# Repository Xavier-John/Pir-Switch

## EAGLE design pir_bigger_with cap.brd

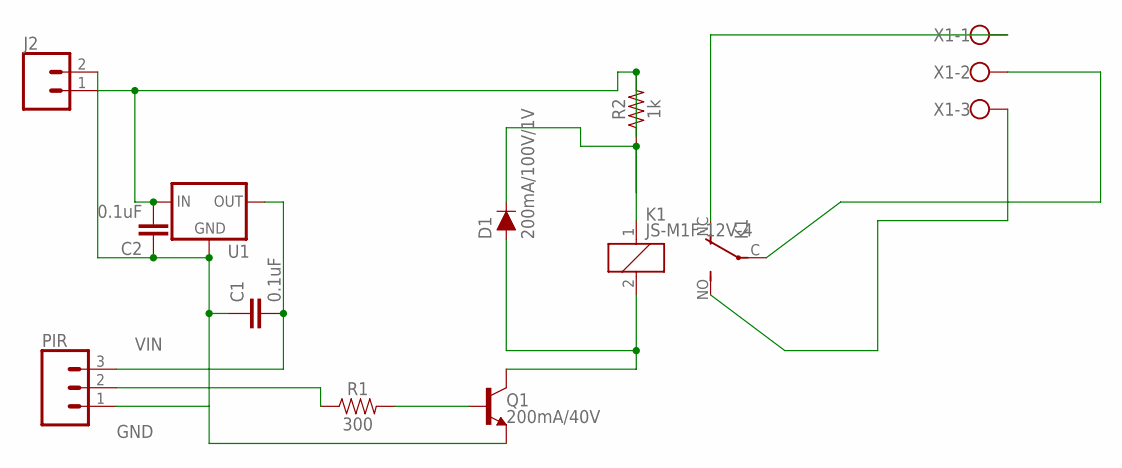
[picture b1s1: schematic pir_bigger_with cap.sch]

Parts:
C1, C2: 0.1uF; CAP-PTH-SMALL-KIT
D1: 200mA/100V/1V; DIODE-1N4148
J2: CONN_025MM; SCREWTERMINAL-5MM-2
K1: JS-M1F-12V-4; JS-M
PIR: CONN_03LONGPADS; 1X03_LONGPADS
Q1: 200mA/40V; TO-92
R1: 300; AXIAL-0.3
R2: 1k; AXIAL-0.3
U1: V_REG_78XXSINK; TO220-IGO
X1: W237-103

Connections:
GND: C1.1, C2.1, J2.2, PIR.1, Q1.1 (E), U1.GND
unnamed: C2.2, J2.1, R2.P$2 (2), U1.IN
unnamed: K1.C, X1.2
unnamed: PIR.2, R1.P$1 (1)
unnamed: Q1.2 (B), R1.P$2 (2)
unnamed: D1.A, K1.2, Q1.3 (C)
unnamed: K1.NC (O), X1.1
unnamed: K1.NO (S), X1.3
unnamed: D1.C, K1.1, R2.P$1 (1)
VIN: C1.2, PIR.3, U1.OUT

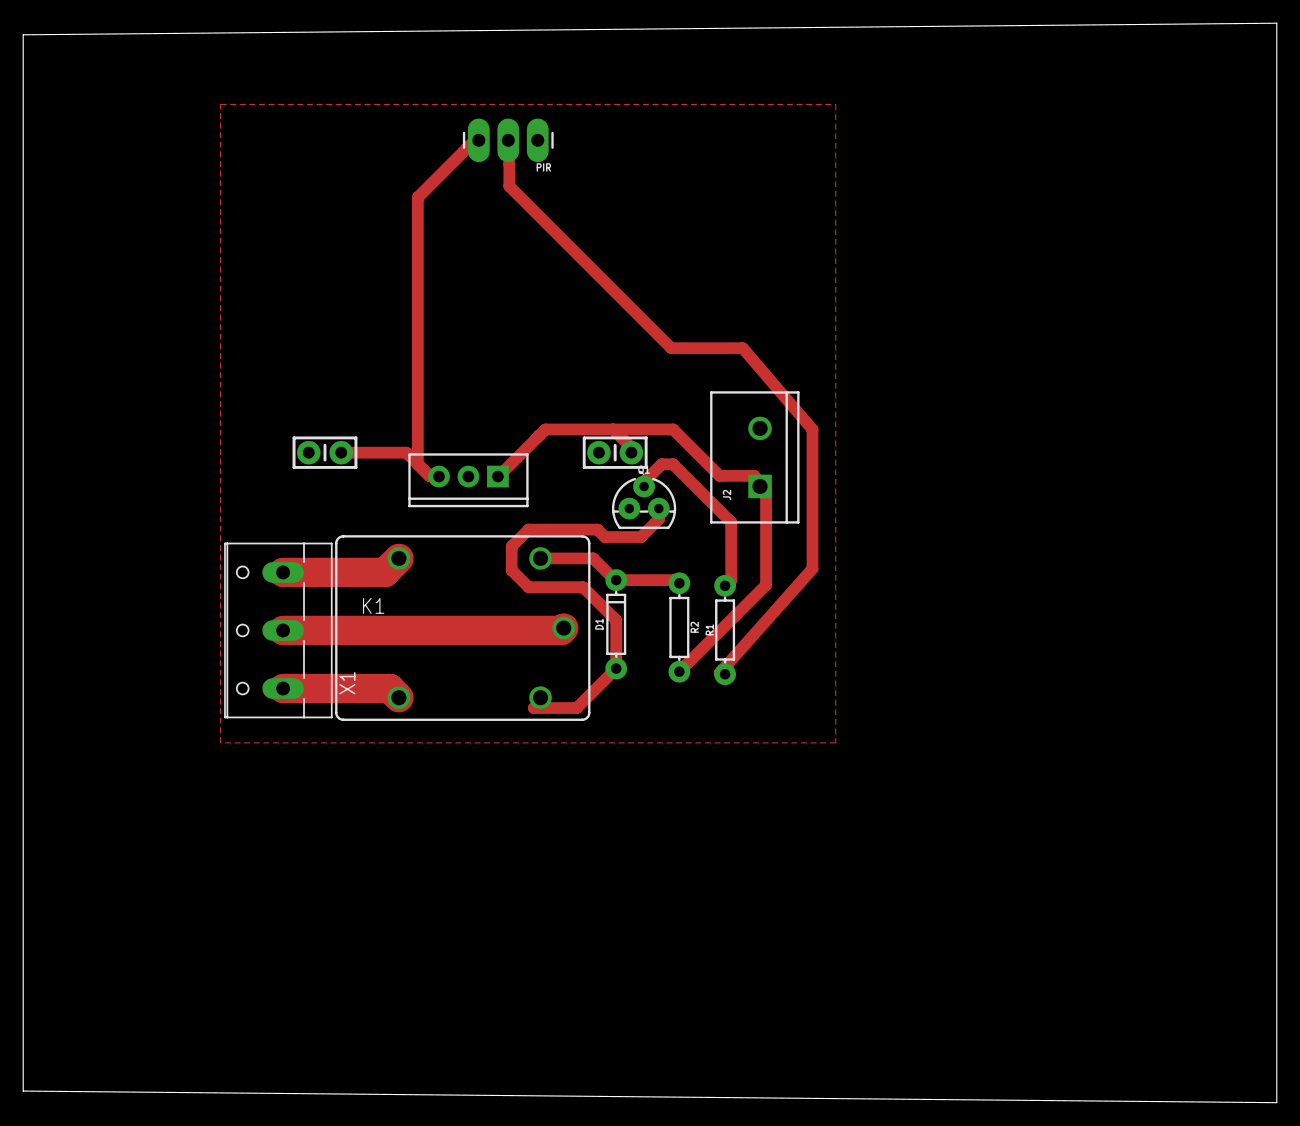
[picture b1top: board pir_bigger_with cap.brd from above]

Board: 2 copper layers, 108.0 x 93.0 mm, 11 parts (0 on the bottom side), 10 nets.

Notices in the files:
parts and their libraries:
SparkFun-DiscreteSemi: Licensing: Creative Commons ShareAlike 4.0 International - https://creativecommons.org/licenses/by-sa/4.0
